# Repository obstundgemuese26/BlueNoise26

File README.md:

### Open-source Wireless Jamming Pentesting Device using ESP32-WROOM-32U & 2 NRFL01+PA+LNA Modules

 ---
# WHAT DOES IT DO?

**IT CREATES NOISE SIGNAL TO JAM BLUETOOTH AND WIFI USING NRF24L01 AND ESP32 IN RANGE 2.4GHZ DEVICES, EFFECTS MAY VARY DEPENDS ON DEVICE BLUETOOTH VERSIONS....WARNING!!! JAMMING IS ILLEGAL**

---

## REQUIRED DEVICE AND MODULE:
1. `NRF24L01+ PLUS – PA LNA SMA Antenne`
-  

2. `1pc ESP32U` 
- 

3. `25V 47UF CAPACITORF` 
- 

4. `1 DIP SWITCH` 
- 

5. `DC Voltage Regulator Step Down Converter 4.5 V-12 V to 3.3 V/5 V 800 mA Power Supply Regulator Adjustment (5 Volt)` 
- 

6. `9V Alkaline Batteries` 
- 

7. `9V Battery Holder` 
- 

---
 ## CUSTOMIZED PCB BOARD IN EAGLE
 ### Brd File
 [Download PCB Files](pcb-board/BlueNoise-pcb-board.brd)

  ### Sch File
 [Download PCB Files](pcb-board/BlueNoise-pcb-board.sch)

---
 ## PINS TO ATTACH NRF24L01 TO ESP32

### FOR DUAL/TWO NRF24L01 
+ ` HSPI= SCK = 14, MISO = 12, MOSI = 13, CS = 15 , CE = 16`
+ ` VSPI= SCK = 18, MISO =19, MOSI = 23 ,CS =21 ,CE = 22`

### FOR SINGLE/ONE NRF24L01 YOU CAN CHOOSE BETWEEN HSPI OR VSPI 
 - `VSPI= SCK = 18, MISO =19, MOSI = 23 ,CS =21 ,CE = 22`
- `HSPI= SCK = 14, MISO = 12, MOSI = 13, CS = 15 , CE = 16` 

---

### Wiring

---

## UPLOADING CODE TO ESP32
Connect ESP to your laptop
 
 1. `Download and install library "RF24 Master" in Arduino/ IDE`
 [Download RF24 Master](arduino/RF24-master(1).zip)

  2. `Download and install library "Button Master" in Arduino/ IDE`
 [Download Button Master](arduino/button-master(1).zip)

  3. Install ESP32 Board: Tools -> Board -> BoardManager <br>
  Search for: ESP -> select: "esp32 by Espressif Sytems" & click "Install"

  3. `Download the dual pin code and upload it in Arduino/ IDE`
 [Download Code](arduino/FORDUALPINS.ino)

## OR USE A WEBFLASHER: NO NEED TO DOWNLOAD INO FILE (USE CHROME OR MICROSOFT BROWSER) [WEBFLASHER](https://simonweckert.com/au5st3llung/COCO/flash/bluenoise/index.html) SELECT WHAT TO UPLOAD VSPI,HSPI OR DUAL AND CHOOSE RIGHT COM PORT
---

# SPECIAL THANKS
  * [ATOMNFT](https://github.com/dkyazzentwatwa/cypher-jammer?tab=readme-ov-file) - Cypher Jammer

  ---

# TROUBLESHOOTING

### python -m esptool --port COM3 --baud 115200 erase_flash

   ---

###  Phase 1: The Clean Slate (Complete Erase)

We will use a very slow speed (115200) to ensure stability.
Open CMD and type (don't hit enter yet):
python -m esptool --port COM3 --baud 115200 erase_flash
Hold the BOOT button on the ESP32.
Tap the EN/RST button once.
Hit Enter on your keyboard.
Release BOOT only after you see "Erasing..."

###  Phase 2: The Manual "Hard-Wire" (If Phase 1 fails)

If the buttons aren't triggering the bootloader, we bypass them with a jumper wire.
Connect a wire from GPIO 0 to GND.
Unplug and replug the USB.
Run the command:
python -m esptool --port COM3 --baud 115200 erase_flash

If it succeeds, remove the wire before trying to upload code again.

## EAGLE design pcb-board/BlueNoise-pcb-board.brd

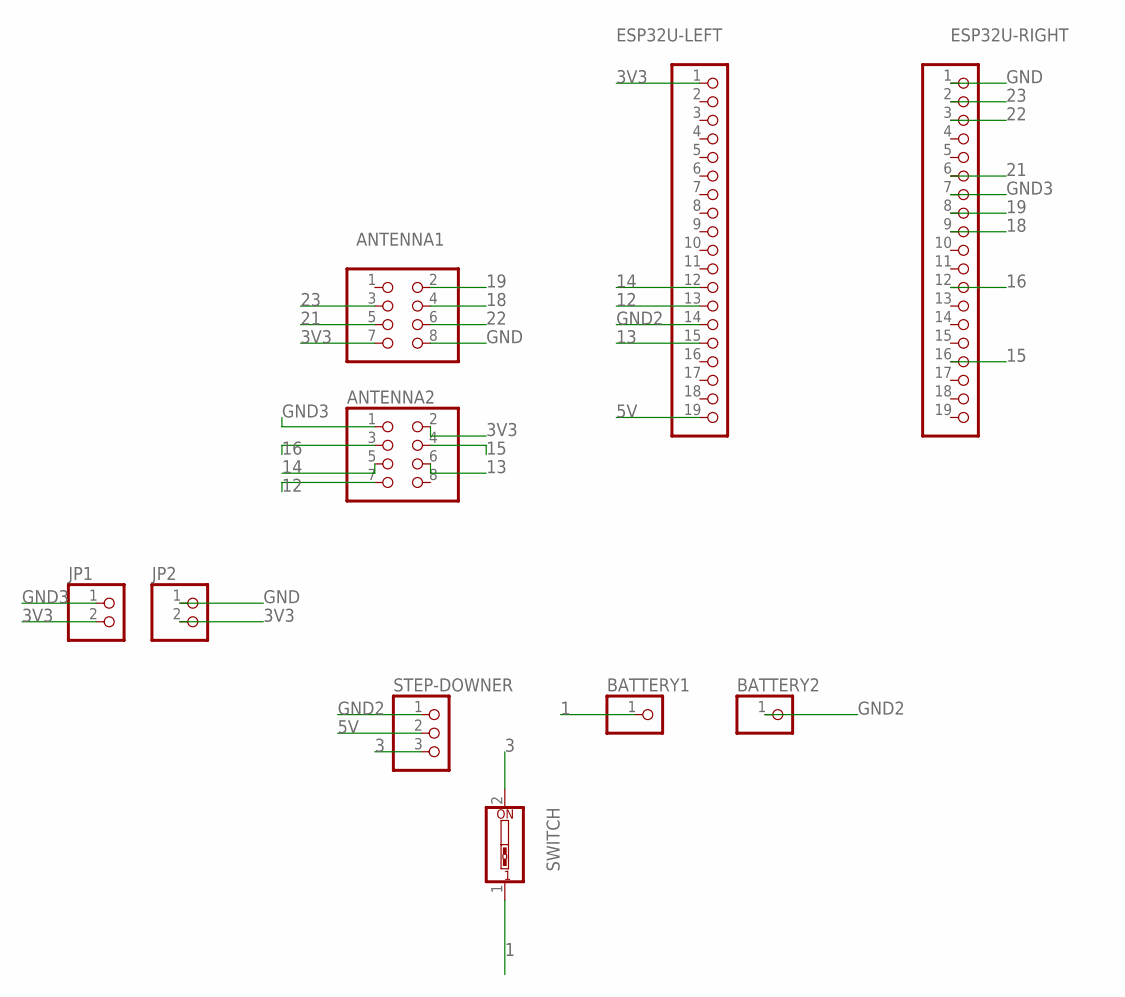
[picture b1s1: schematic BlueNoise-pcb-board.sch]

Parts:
ANTENNA1, ANTENNA2: PINHD-2X4; 2X04
BATTERY1, BATTERY2: PINHD-1X1; 1X01
ESP32U-LEFT, ESP32U-RIGHT: PINHD-1X19; 1X19
JP1, JP2: PINHD-1X2; 1X02
STEP-DOWNER: PINHD-1X3; 1X03
SWITCH: SW_DIP-1; EDG-01

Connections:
1: BATTERY1.1, SWITCH.1
3: STEP-DOWNER.3, SWITCH.2
3V3: ANTENNA1.7, ANTENNA2.2, ESP32U-LEFT.1, JP1.2, JP2.2
5V: ESP32U-LEFT.19, STEP-DOWNER.2
12: ANTENNA2.7, ESP32U-LEFT.13
13: ANTENNA2.6, ESP32U-LEFT.15
14: ANTENNA2.5, ESP32U-LEFT.12
15: ANTENNA2.4, ESP32U-RIGHT.16
16: ANTENNA2.3, ESP32U-RIGHT.12
18: ANTENNA1.4, ESP32U-RIGHT.9
19: ANTENNA1.2, ESP32U-RIGHT.8
21: ANTENNA1.5, ESP32U-RIGHT.6
22: ANTENNA1.6, ESP32U-RIGHT.3
23: ANTENNA1.3, ESP32U-RIGHT.2
GND: ANTENNA1.8, ESP32U-RIGHT.1, JP2.1
GND2: BATTERY2.1, ESP32U-LEFT.14, STEP-DOWNER.1
GND3: ANTENNA2.1, ESP32U-RIGHT.7, JP1.1

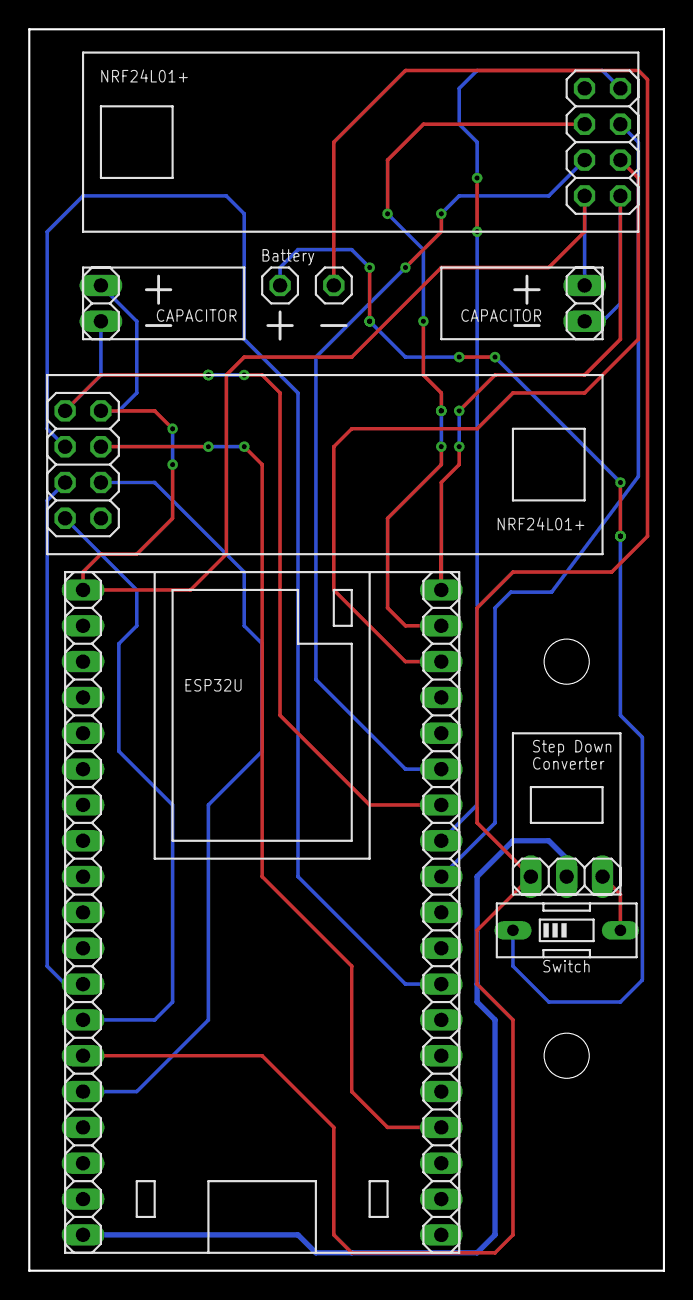
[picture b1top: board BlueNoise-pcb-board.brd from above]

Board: 2 copper layers, 45.0 x 88.0 mm, 12 parts (0 on the bottom side), 17 nets.

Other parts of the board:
U$2, U$3: M3HOLE

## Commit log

2026-05-20 Create images
2026-05-20 Create arduino
2026-05-20 Create pcb-board
2026-05-20 Create web
